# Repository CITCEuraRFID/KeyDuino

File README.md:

## KeyDuino Library

Welcome to KeyDuino official GitHub repository!  
Here you will find all the files you need to develop programs for your KeyDuino.  
You can also look at the [wiki](https://github.com/CITCEuraRFID/KeyDuino/wiki) for informations about KeyDuino and its capabilities.  

The library is still under development, and everything is not perfect yet!  
That is why we would be very glad to hear from you about your experience with KeyDuino library ; if you encounter any problem, please feel free to open issues or contact us directly: that way we will be able to correct errors and improve the library.

### Tutorials & Projects
If you want to discover what you can do with your KeyDuino, join http://keyduino.forumsactifs.com/ !  
There you will find projects ideas, discussions, and tutorials, to help you get the best from your KeyDuino.  
If you have ideas to share, or questions to ask, don't hesitate! We would be very glad to hear from you.  

### Content
In this repository, you will find pretty much everything we develop for KeyDuino.

```
/---KeyDuino                  //The root folder of the repository  
|   +---KeyDuino              //The lib subfolder you need to put in your Arduino/libraries folder  
|   |   +---examples          //All the examples supplied within the lib  
|   |   |   +---projects      //Examples associated with KeyDuino projects  
|   |   |   +---NDEF          //Examples using the NDEF lib you need to download separately  
|   |   |   +---...  
|   |   |  
|   |   +---...  
|   |
|   +---KeyDuinoESP           //An implementation of KeyDuino with ESP module for WiFi communication  
|   |   +---ESP               //Files for the ESP  
|   |   +---KeyDuino          //Files for the KeyDuino  
|   |  
|   +---android_app           //The folder containing everything about Android application  
|   |   +---nfc_talker.apk    //The apk of the Android application we developped  
|   |    
|   +---hardware              //All hardware files of KeyDuino  
|   |   +---3D_printed_case   //STL files for 3D printed case
|   |   +---KeyDuino_board    //Hardware files for KeyDuino board  
|   |   +---antenna           //Hardware files for KeyDuino remote antenna  
```

### Compatibility
KeyDuino library is made to be used with [KeyDuino board](https://www.kickstarter.com/projects/1535978353/keyduino), but it also works by default with a classical Arduino Leonardo using a PN532 Shield, as long as communication is done through HSU.

### Contribution
KeyDuino library is based on Adafruit_NFCShield_I2C, with improvements by Seeed Studio, and HSU (High Speed Uart) driver added by Elechouse.

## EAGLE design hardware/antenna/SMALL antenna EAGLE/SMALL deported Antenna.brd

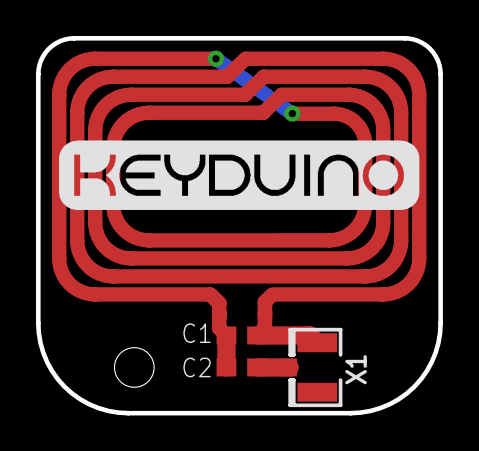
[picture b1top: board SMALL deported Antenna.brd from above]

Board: 2 copper layers, 22.4 x 20.8 mm, 4 parts (0 on the bottom side), 3 nets.

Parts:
C1: 390p; C0603
C2: 68p; C0603
U$1: ANT_V7; ANT_13.56_P7
X1: U.FL

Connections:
unnamed: C2.2, X1.3
unnamed: C1.2, U$1.TX2, X1.1, X1.2
unnamed: C1.1, C2.1, U$1.TX1

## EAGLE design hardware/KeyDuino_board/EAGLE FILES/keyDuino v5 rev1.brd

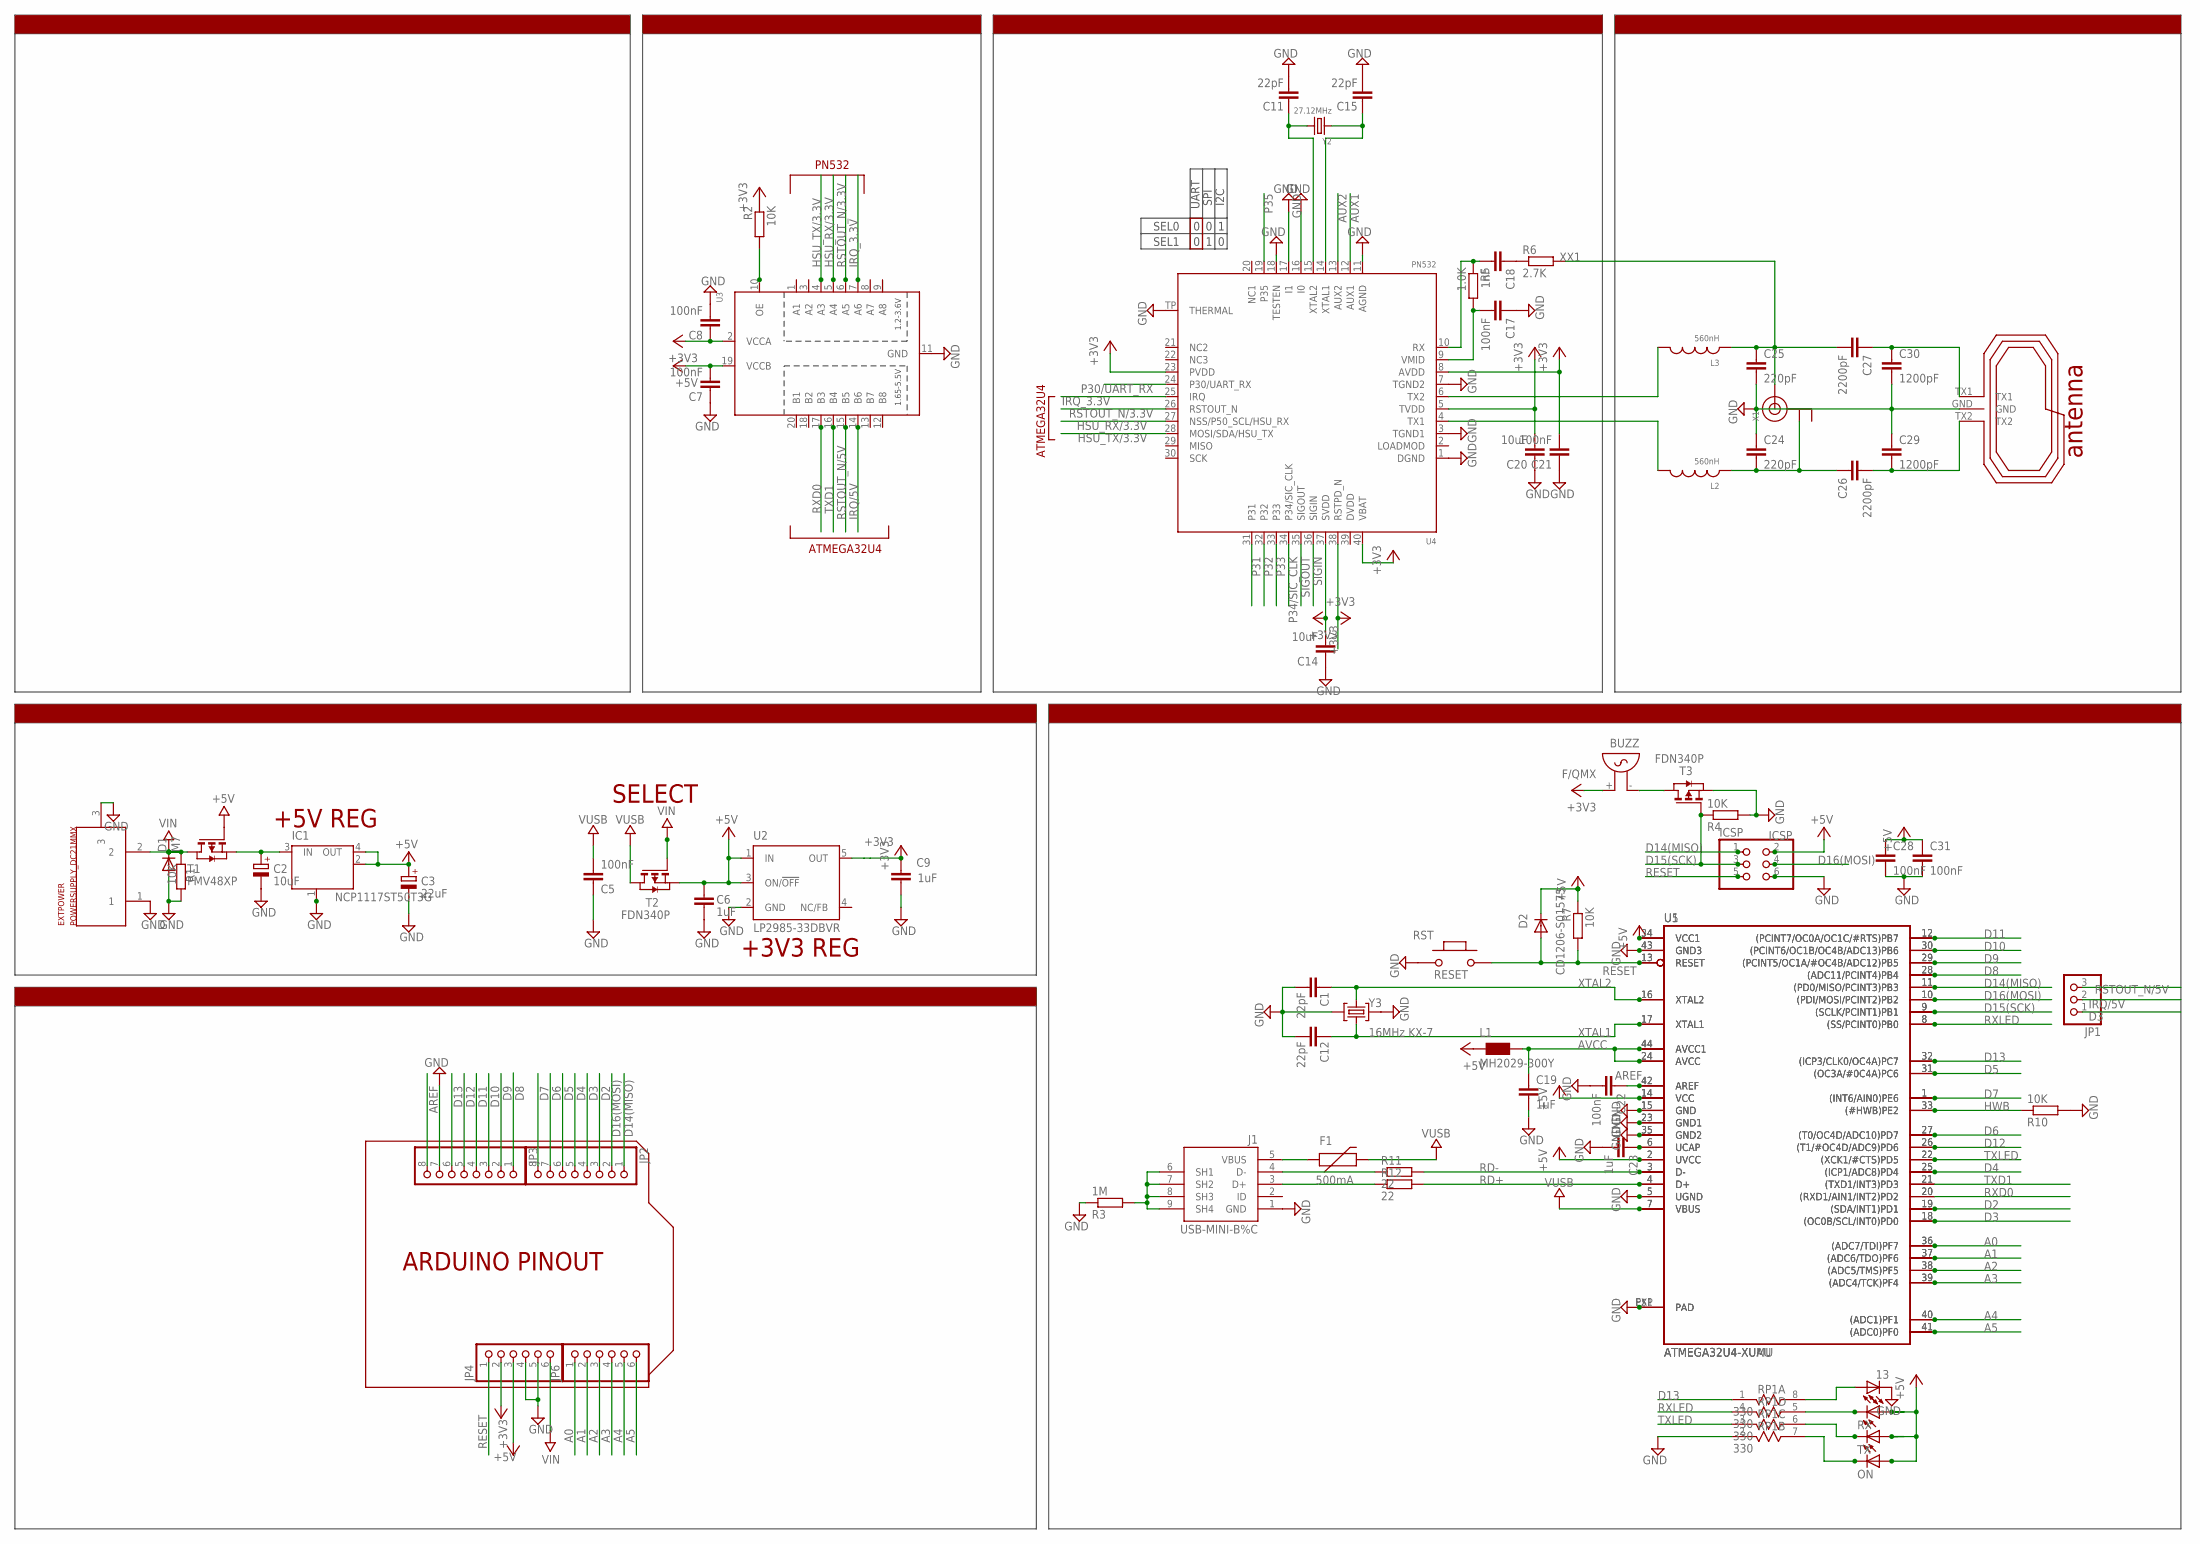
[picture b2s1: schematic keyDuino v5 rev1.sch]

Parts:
13: LEDCHIPLED_0603; CHIPLED_0603
BUZZ: F/QMX
C1, C11, C12, C15: 22pF; 0603-CAP
C2: 10uF; SMC_B
C3: 22uF; SMC_B
C5, C7, C8, C17, C22, C28, C31: 100nF; C0603
C6, C9, C19, C23: 1uF; C0603
C14, C20: 10uF; C0805
C18: 1nF; C0603
C21: 100nF; C0805
C24, C25: 220pF; C0603
C26, C27: 2200pF; C0603
C29, C30: 1200pF; C0603
D1: M7; SMB
D2: CD1206-S01575; MINIMELF
EXTPOWER: POWERSUPPLY_DC21MMX; POWERSUPPLY_DC-21MM
F1: 500mA; PTC-1206
IC1: NCP1117ST50T3G; SOT223
ICSP: ICSP; 2X03
J1: USB-MINI-B%C; USB-MINI-B_2
JP1: PINHD-1X3; 1X03
JP2, JP3: PINHD-1X8CLEANBIG; 1X08-CLEANBIG
JP4, JP6: PINHD-1X6CB; 1X06-CLEANBIG
L1: MH2029-300Y; 0805
L2, L3: 560nH; 0805@1
ON: LEDCHIPLED_0603; CHIPLED_0603
R1, R2, R4, R7, R10: 10K; R0603
R3: 1M; R0805
R5: 1.0K; R0603
R6: 2.7K; R0603
R11, R12: 22; R0603
RP1: 330; RES4NT
RST: RESET; 157SW
RX: LEDCHIPLED_0603; CHIPLED_0603
T1: PMV48XP; SOT-23
T2, T3: FDN340P; SOT-23
TX: LEDCHIPLED_0603; CHIPLED_0603
U1: ATMEGA32U4-XUAU; TQFP44-PAD
U2: LP2985-33DBVR; SOT23-DBV
U3: TXB0108PWR; TSSOP20
U4: PN532; HVQFN40-6X6
U5: ATMEGA32U4-XUMU; QFN44ML7X7
U$1: ANT_V3; ANT_13.56_P4
X1: ANTENNA_U.FL; U.FL
Y2: 27.12MHz; CRYSTAL_3.2X2.5
Y3: 16MHz KX-7; CRYSTAL-3.2-2.5

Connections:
+3V3: BUZZ.+ (2), C8.1, C9.2, C14.2, C20.2, C21.2, JP4.2, R2.1, U2.5 (OUT), U3.2 (VCCA), U4.5 (TVDD), U4.8 (AVDD), U4.23 (PVDD), U4.37 (SVDD), U4.38 (RSTPD_N), U4.40 (VBAT)
+5V: C3.+, C6.2, C7.2, C28.1, C31.1, D2.C, IC1.2 (OUT), IC1.4 (OUT), ICSP.2, JP4.3, L1.1, ON.A, R7.1, RX.A, T1.3 (G), T2.2 (S), TX.A, U1.2 (UVCC), U1.14 (VCC), U1.34 (VCC1), U2.1 (IN), U2.3 (ON/!OFF), U3.19 (VCCB), U5.2 (UVCC), U5.14 (VCC), U5.34 (VCC1)
A0: JP6.1, U1.36 ((ADC7/TDI)PF7), U5.36 ((ADC7/TDI)PF7)
A1: JP6.2, U1.37 ((ADC6/TDO)PF6), U5.37 ((ADC6/TDO)PF6)
A2: JP6.3, U1.38 ((ADC5/TMS)PF5), U5.38 ((ADC5/TMS)PF5)
A3: JP6.4, U1.39 ((ADC4/TCK)PF4), U5.39 ((ADC4/TCK)PF4)
A4: JP6.5, U1.40 ((ADC1)PF1), U5.40 ((ADC1)PF1)
A5: JP6.6, U1.41 ((ADC0)PF0), U5.41 ((ADC0)PF0)
AREF: C22.1, JP3.8, U1.42 (AREF), U5.42 (AREF)
AUX1: U4.12 (AUX1)
AUX2: U4.13 (AUX2)
AVCC: C19.1, L1.2, U1.24 (AVCC), U1.44 (AVCC1), U5.24 (AVCC), U5.44 (AVCC1)
B1: 13.A, RP1.8 (2)
CON1: C24.2, C26.1, L2.1, X1.1 (GND)
D2: JP2.3, U1.19 ((SDA/INT1)PD1), U5.19 ((SDA/INT1)PD1)
D3: JP1.1, JP2.4, U1.18 ((OC0B/SCL/INT0)PD0), U5.18 ((OC0B/SCL/INT0)PD0)
D4: JP2.5, U1.25 ((ICP1/ADC8)PD4), U5.25 ((ICP1/ADC8)PD4)
D5: JP2.6, U1.31 ((OC3A/#0C4A)PC6), U5.31 ((OC3A/#0C4A)PC6)
D6: JP2.7, U1.27 ((T0/OC4D/ADC10)PD7), U5.27 ((T0/OC4D/ADC10)PD7)
D7: JP2.8, U1.1 ((INT6/AIN0)PE6), U5.1 ((INT6/AIN0)PE6)
D8: JP3.1, U1.28 ((ADC11/PCINT4)PB4), U5.28 ((ADC11/PCINT4)PB4)
D9: JP3.2, U1.29 ((PCINT5/OC1A/#OC4B/ADC12)PB5), U5.29 ((PCINT5/OC1A/#OC4B/ADC12)PB5)
D10: JP3.3, U1.30 ((PCINT6/OC1B/OC4B/ADC13)PB6), U5.30 ((PCINT6/OC1B/OC4B/ADC13)PB6)
D11: JP3.4, U1.12 ((PCINT7/OC0A/OC1C/#RTS)PB7), U5.12 ((PCINT7/OC0A/OC1C/#RTS)PB7)
D12: JP3.5, U1.26 ((T1/#OC4D/ADC9)PD6), U5.26 ((T1/#OC4D/ADC9)PD6)
D13: JP3.6, RP1.1, U1.32 ((ICP3/CLK0/OC4A)PC7), U5.32 ((ICP3/CLK0/OC4A)PC7)
D14(MISO): ICSP.1, JP2.1, U1.11 ((PD0/MISO/PCINT3)PB3), U5.11 ((PD0/MISO/PCINT3)PB3)
D15(SCK): ICSP.3, R4.1, T3.3 (G), U1.9 ((SCLK/PCINT1)PB1), U5.9 ((SCLK/PCINT1)PB1)
D16(MOSI): ICSP.4, JP2.2, U1.10 ((PDI/MOSI/PCINT2)PB2), U5.10 ((PDI/MOSI/PCINT2)PB2)
G1: RP1.5 (2), RX.C
GND: 13.C, C1.1, C2.-, C3.-, C5.1, C6.1, C7.1, C8.2, C9.1, C11.1, C12.1, C14.1, C15.1, C17.1, C19.2, C20.1, C21.1, C22.2, C23.2, C24.1, C25.2, C28.2, C29.1, C30.2, C31.2, D1.A, EXTPOWER.1, EXTPOWER.3, IC1.1 (GND/ADJ), ICSP.6, J1.1 (GND), JP3.7, JP4.4, JP4.5, R1.1, R3.1, R4.2, R10.2, RP1.2 (1), RST.1, T3.2 (S), U1.5 (UGND), U1.15 (GND), U1.23 (GND1), U1.35 (GND2), U1.43 (GND3), U1.P$1 (PAD), U2.2 (GND), U3.11 (GND), U4.1 (DGND), U4.3 (TGND1), U4.7 (TGND2), U4.11 (AGND), U4.16 (I0), U4.17 (I1), U4.18 (TESTEN), U4.TP (THERMAL), U5.5 (UGND), U5.15 (GND), U5.23 (GND1), U5.35 (GND2), U5.43 (GND3), U5.EXP (PAD), U$1.GND, Y3.2 (GND), Y3.4 (GND)
HSU_RX/3.3V: U3.5 (A4), U4.27 (NSS/P50_SCL/HSU_RX)
HSU_TX/3.3V: U3.4 (A3), U4.28 (MOSI/SDA/HSU_TX)
HWB: R10.1, U1.33 ((#HWB)PE2), U5.33 ((#HWB)PE2)
IRQ/5V: JP1.2, U3.14 (B6)
IRQ_3.3V: U3.7 (A6), U4.25 (IRQ)
unnamed: BUZZ.- (1), T3.1 (D)
unnamed: F1.1, J1.5 (VBUS)
unnamed: J1.6 (SH1), J1.7 (SH2), J1.8 (SH3), J1.9 (SH4), R3.2
unnamed: C18.1, R6.1
unnamed: L2.2, U4.4 (TX1)
unnamed: L3.2, U4.6 (TX2)
unnamed: ON.C, RP1.7 (2)
unnamed: J1.4 (D-), R11.1
unnamed: J1.3 (D+), R12.1
unnamed: C2.+, IC1.3 (IN), T1.2 (S)
unnamed: R2.2, U3.10 (OE)
unnamed: C15.2, U4.14 (XTAL1), Y2.1
unnamed: C11.2, U4.15 (XTAL2), Y2.2
unnamed: C17.2, R5.2, U4.9 (VMID)
unnamed: C18.2, R5.1, U4.10 (RX)
P30/UART_RX: U4.24 (P30/UART_RX)
P31: U4.31
P32: U4.32
P33: U4.33
P34/SIC_CLK: U4.34 (P34/SIC_CLK)
P35: U4.19 (P35)
R1: RP1.6 (2), TX.C
RD+: R12.2, U1.4 (D+), U5.4 (D+)
RD-: R11.2, U1.3 (D-), U5.3 (D-)
RESET: D2.A, ICSP.5, JP4.1, R7.2, RST.2, U1.13 (RESET), U5.13 (RESET)
RSTOUT_N/3.3V: U3.6 (A5), U4.26 (RSTOUT_N)
RSTOUT_N/5V: JP1.3, U3.15 (B5)
RXD0: U1.20 ((RXD1/AIN1/INT2)PD2), U3.17 (B3), U5.20 ((RXD1/AIN1/INT2)PD2)
RXLED: RP1.4 (1), U1.8 ((SS/PCINT0)PB0), U5.8 ((SS/PCINT0)PB0)
SIGIN: U4.36 (SIGIN)
SIGOUT: U4.35 (SIGOUT)
TX1_ANTENNA: C26.2, C29.2, U$1.TX2
TX2_ANTENNA: C27.1, C30.1, U$1.TX1
TXD1: U1.21 ((TXD1/INT3)PD3), U3.16 (B4), U5.21 ((TXD1/INT3)PD3)
TXLED: RP1.3 (1), U1.22 ((XCK1/#CTS)PD5), U5.22 ((XCK1/#CTS)PD5)
UCAP: C23.1, U1.6 (UCAP), U5.6 (UCAP)
VIN: D1.C, EXTPOWER.2, JP4.6, R1.2, T1.1 (D), T2.3 (G)
VUSB: C5.2, F1.2, T2.1 (D), U1.7 (VBUS), U5.7 (VBUS)
XTAL1: C12.2, U1.17 (XTAL1), U5.17 (XTAL1), Y3.1 (C1)
XTAL2: C1.2, U1.16 (XTAL2), U5.16 (XTAL2), Y3.3 (C2)
XX1: C25.1, C27.2, L3.1, R6.2, X1.3 (SIGNAL)

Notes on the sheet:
ATMEGA32U4
+3V3 REG
SEL0
SEL1
UART
SPI
I2C
SELECT
SUPPLYs
+5V REG
convertisseur de niveau
PN532
ACCORDING CIRCUIT
PINOUT
ARDUINO PINOUT
MOD

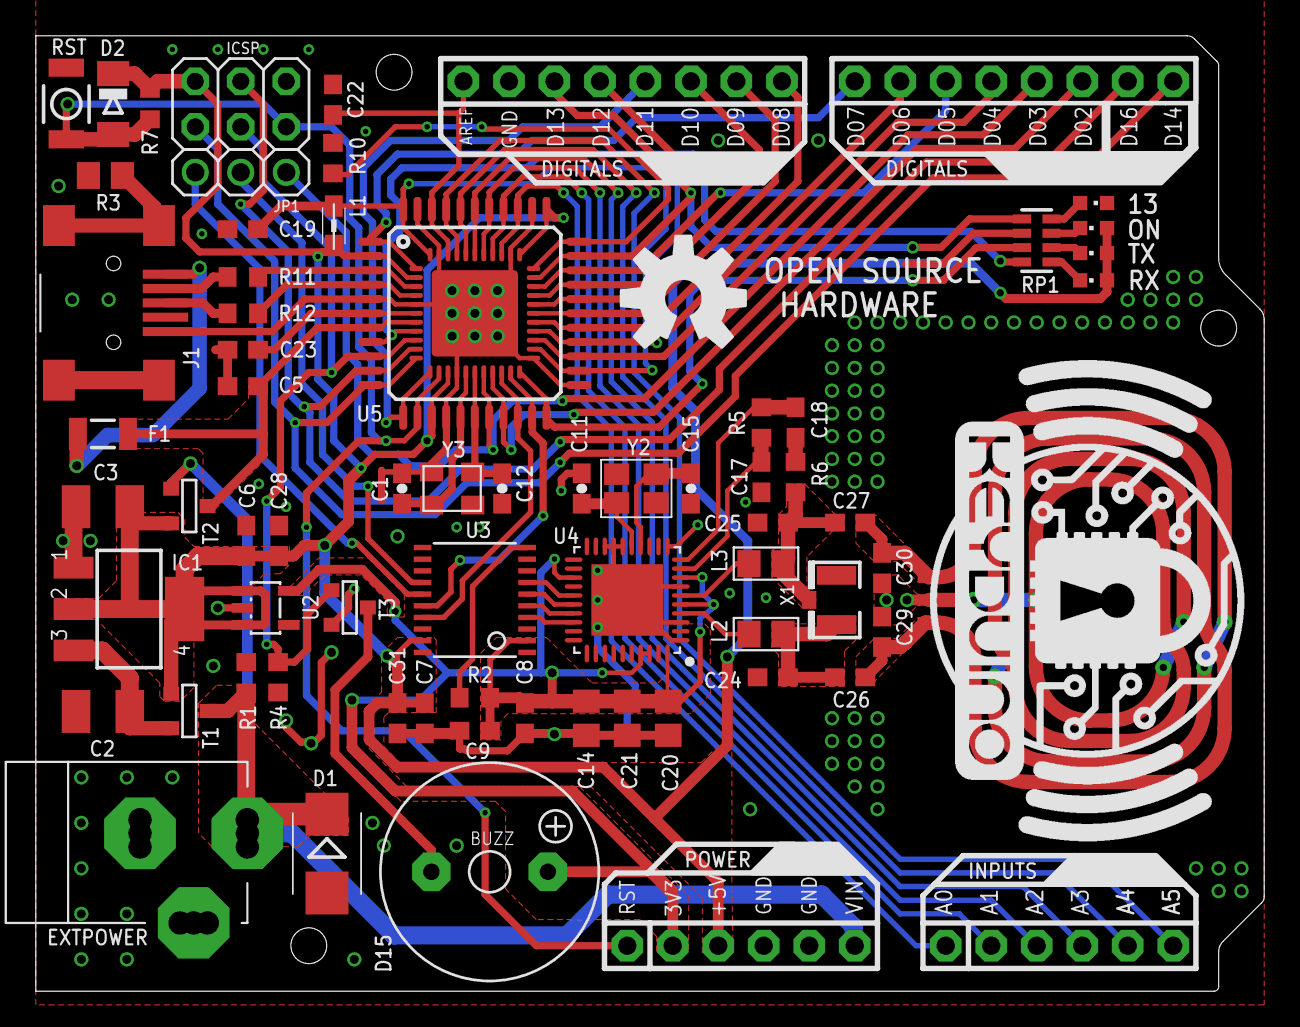
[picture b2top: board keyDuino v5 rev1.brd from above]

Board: 2 copper layers, 68.6 x 53.3 mm, 72 parts (0 on the bottom side), 67 nets.

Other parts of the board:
U$2: OSHW-LOGO-L

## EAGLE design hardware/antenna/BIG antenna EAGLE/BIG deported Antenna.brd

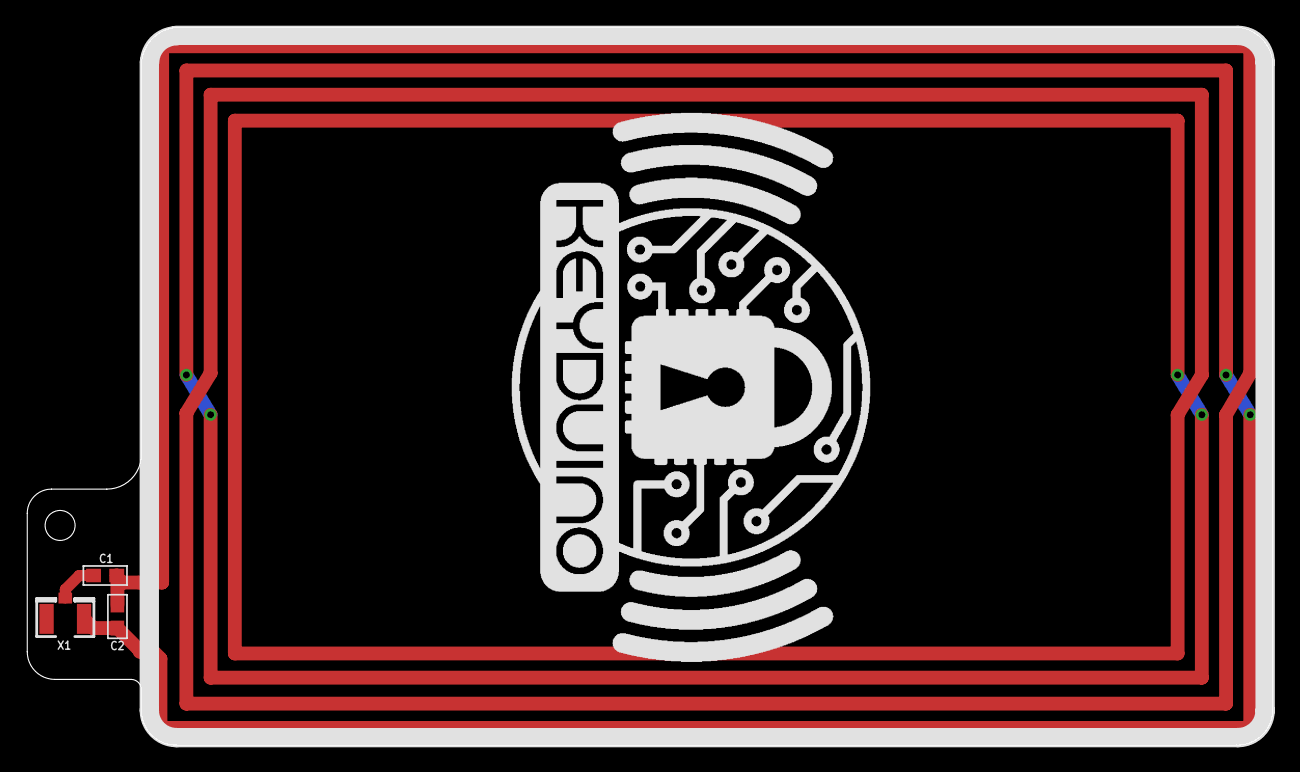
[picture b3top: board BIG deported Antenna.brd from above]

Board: 2 copper layers, 91.4 x 52.7 mm, 4 parts (0 on the bottom side), 3 nets.

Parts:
C1, C2: 22p; 0603
U$1: KEYDUINO_DEPORTED_ANTENNA
X1: U.FL

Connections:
ANT1-TX1: C1.1, X1.3
unnamed: C2.1, U$1.TX2, X1.1, X1.2
TX2_ANTENNA: C1.2, C2.2, U$1.TX1

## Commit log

2016-01-15 Corrects typo /o/
2016-01-15 Removes debugs prints and adds comments
2016-01-18 Add MifareClassicKeyDuino class, which inherits from KeyDuino to provide a simple mifareclassic-dedicated object. Also add example sketch to read mifare classic card.
2016-01-19 Add mifare classic reset example and change methods place.
2016-01-19 Add input waiting to loop
2016-01-21 Change licence location
2016-01-22 Add two more example sketches. Add PN532.h file for compatibility with NDEF library without changing it. (PN532 class basically inherits from KeyDuino)
2016-01-25 Add hardware files
2016-01-25 Improve examples ergonomics.
2016-01-25 Add relay shield example.
2016-01-26 Add write nfc tag example
2016-01-26 Add tag identification example.
2016-01-27 Add compatibility part in readme.
2016-01-27 Add NDEF library examples.
2016-02-05 Added french getting started
2016-02-05 Add Android app APK file.
2016-02-08 Update example.
2016-02-09 Add comments in example.
2016-02-09 Add reauthentication if failure.
2016-02-15 Add english getting started. Not definitive version.
2016-02-17 Improve readme
2016-02-17 Add comments to PN532.h
2016-02-19 Include buzzing function in KeyDuino.cpp
2016-02-19 Remove buzzing old declaration in example.
2016-02-24 Remove serial waiting in examples.
2016-02-24 Standardize baudrate.
2016-03-01 Correct typos in exemples.
2016-03-01 Add example to format a Mifare Classic card to NDEF.
2016-03-03 Add wiki link
2016-03-04 Add NFC Infinity Table example sketch
2016-03-07 Add nfc_logger project
2016-03-07 Add KeyDuino pinout control sketch, to be used with KeyDuino Android Application. This is just an example sketch, not optimized. It just shows the way to communicate with the board and pins. This als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
2016-03-07 Adapt the output of tag_identification to the needed format of ID for other projects
2016-03-07 Add nfc_box example.
2016-03-07 Add link to projects videos
2016-03-08 Add directory tree in README.md
2016-03-09 Correct typos
2016-03-09 UID format clarification
2016-03-09 Corrected byte amount
2016-03-09 Small insignificant changes
2016-03-09 Correct typo
2016-03-14 Add support for recent version of Arduino.
2016-03-14 Update display of app
2016-03-17 Add example to read a NDEF message coming from a NFC active device.
2016-03-21 Correct format
2016-03-21 Add communication with ISO14443B cards. Just grabbing the PUPI and putting it in uid field for now.
2016-03-22 Trying exchanging APDU with ISO14443B cards. Not working yet, but soon ;)
2016-03-23 SELECT_AID now works. The responseLength should be initialized (64 bytes for an ISO14443B card allows enough space)
2016-03-25 Add comments to examples
2016-03-25 Add example on how to exchange APDU commands with card. Supported types, for now, are ISO14443-A and ISO14443-B cards.
2016-03-30 Small changes
2016-03-30 Adapt mifare_read example to changes
2016-03-30 Add tag enlisting when reading ID. Not sure, but shouldn't be a problem.
2016-03-31 Adapt examples to recent changes
2016-04-02 Correct name
2016-04-02 Remove debug
2016-04-04 Move MifareClassic example into a single folder, and add write example
2016-04-07 Remove techno argument
2016-05-31 Optimize order of Mifare default keys
2016-06-15 Added charlier_case stl files
2016-06-15 Add ray_case scad and stl files
2016-07-05 Added new KeyDuino with ESP module
2016-07-05 Optimize control process
2016-07-05 Solve problem with P2P : with some device, it worked only with debug mode ... that may be due to a need for delay.
2016-07-05 Optimize reactivation of tags when authentication failed
2016-07-05 Reorder broker connexion verification after checking for a tag
2016-07-07 Update readme with KeyDuinoESP files

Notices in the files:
parts and their libraries:
SparkFun-Aesthetics: Licensing: Creative Commons ShareAlike 4.0 International - https://creativecommons.org/licenses/by-sa/4.0
